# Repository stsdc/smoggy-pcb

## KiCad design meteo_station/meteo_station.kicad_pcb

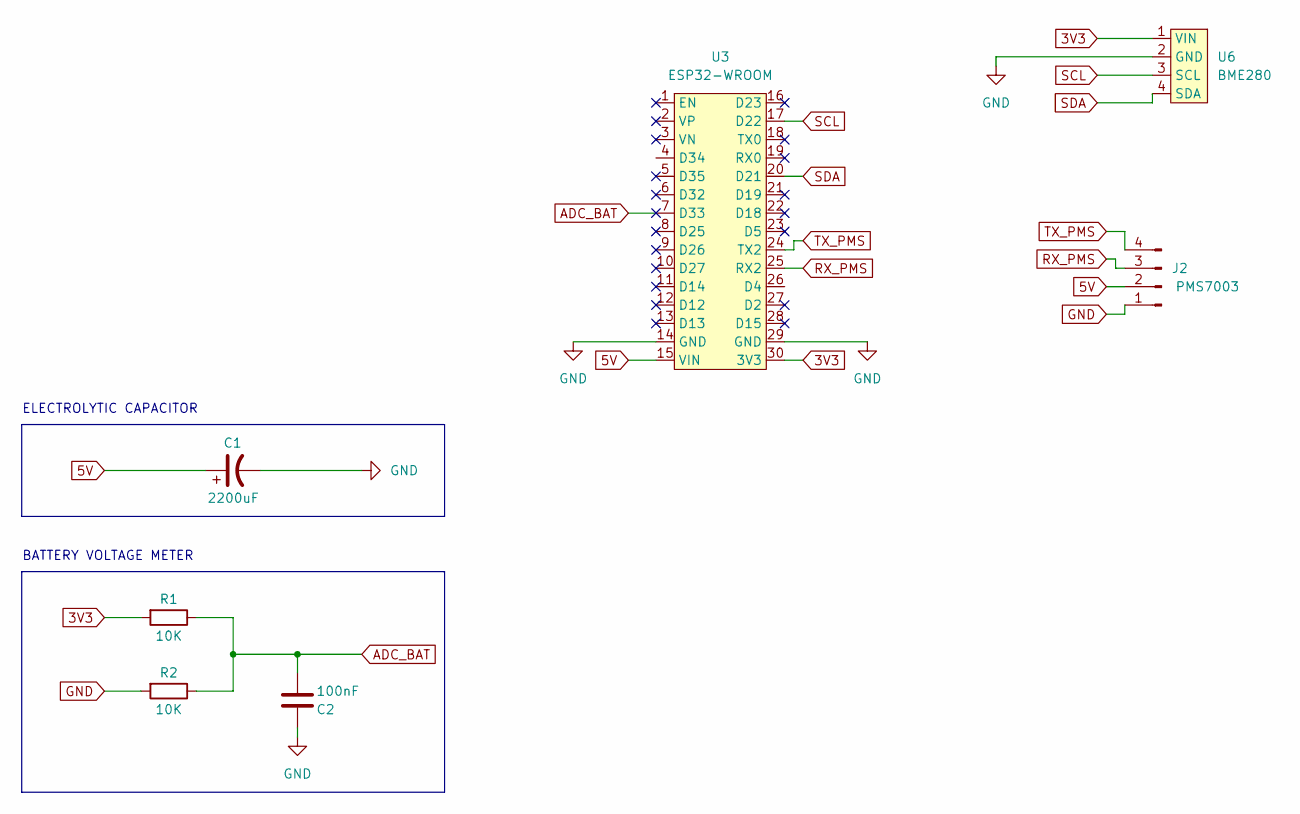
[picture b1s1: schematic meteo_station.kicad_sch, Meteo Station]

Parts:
C1: 2200uF; CP_Radial_D10.0mm_P5.00mm
C2: 100nF; C_Disc_D5.0mm_W2.5mm_P2.50mm
J2: PMS7003; PinHeader_1x04_P2.54mm_Horizontal
R1, R2: 10K; R_Axial_DIN0207_L6.3mm_D2.5mm_P10.16mm_Horizontal
U3: ESP32-WROOM
U6: BME280

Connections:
3V3: R1.2, U3.30 (3V3), U6.1 (VIN)
5V: C1.1, J2.2, U3.15 (VIN)
ADC_BAT: C2.1, R1.1, R2.1, U3.7 (D33)
GND: C1.2, C2.2, J2.1, R2.2, U3.14 (GND), U3.29 (GND), U6.2 (GND)
RX_PMS: J2.3, U3.25 (RX2)
SCL: U3.17 (D22), U6.3 (SCL)
SDA: U3.20 (D21), U6.4 (SDA)
TX_PMS: J2.4, U3.24 (TX2)

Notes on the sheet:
ELECTROLYTIC CAPACITOR
BATTERY VOLTAGE METER

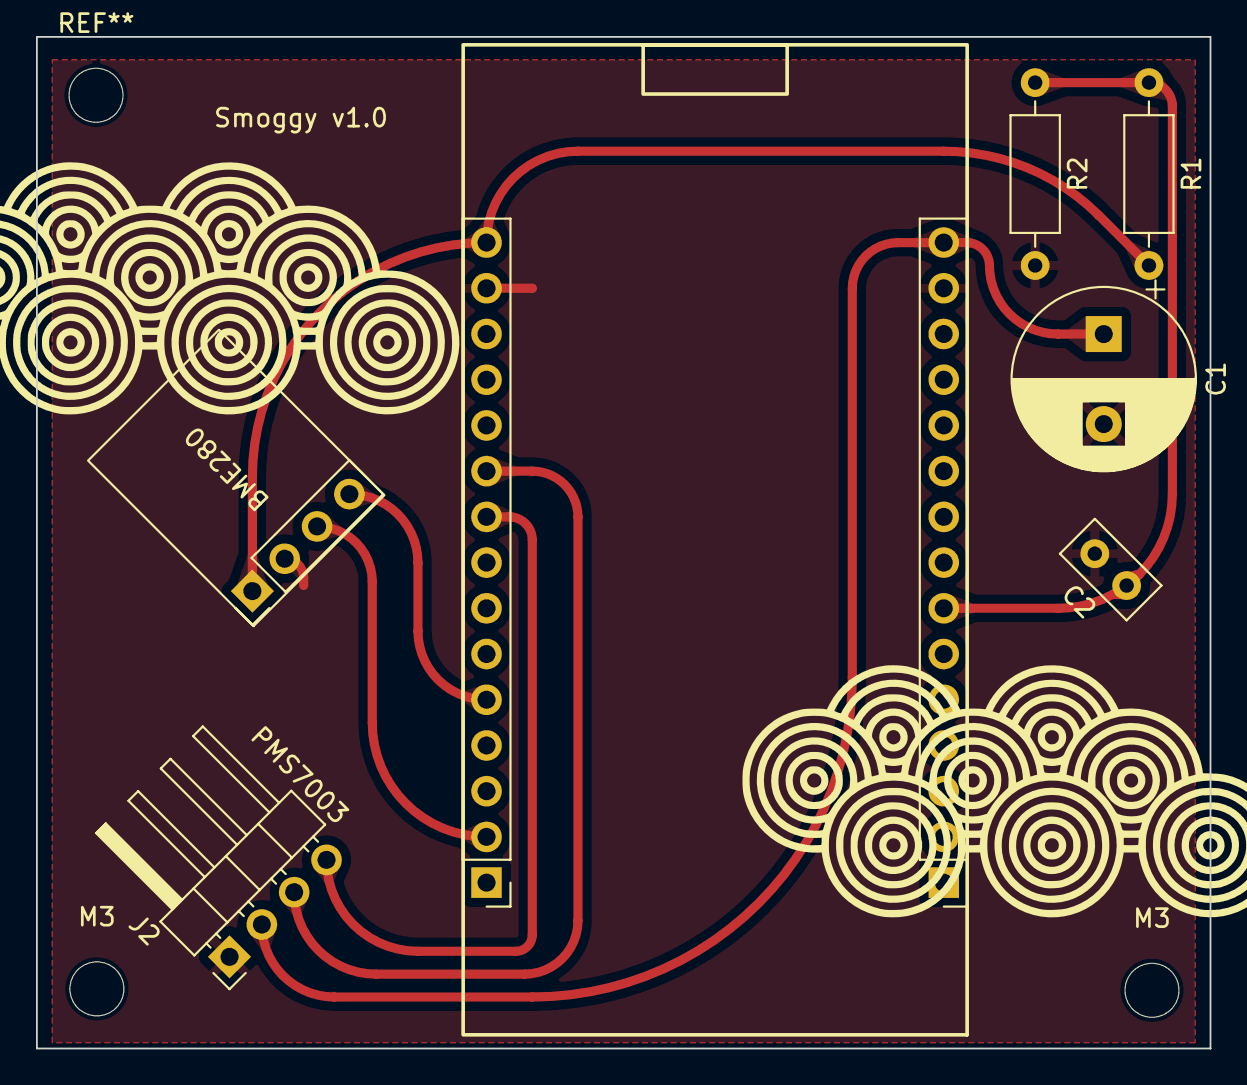
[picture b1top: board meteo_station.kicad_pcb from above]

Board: 2 copper layers, 65.2 x 56.2 mm, 9 parts (0 on the bottom side), 8 nets.

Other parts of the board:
M3, M3#2: MountingHole_3mm

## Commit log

2023-05-03 something
2023-05-06 something2
